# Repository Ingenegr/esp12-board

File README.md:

# esp12-board
esp-12 Board Design Eagle File

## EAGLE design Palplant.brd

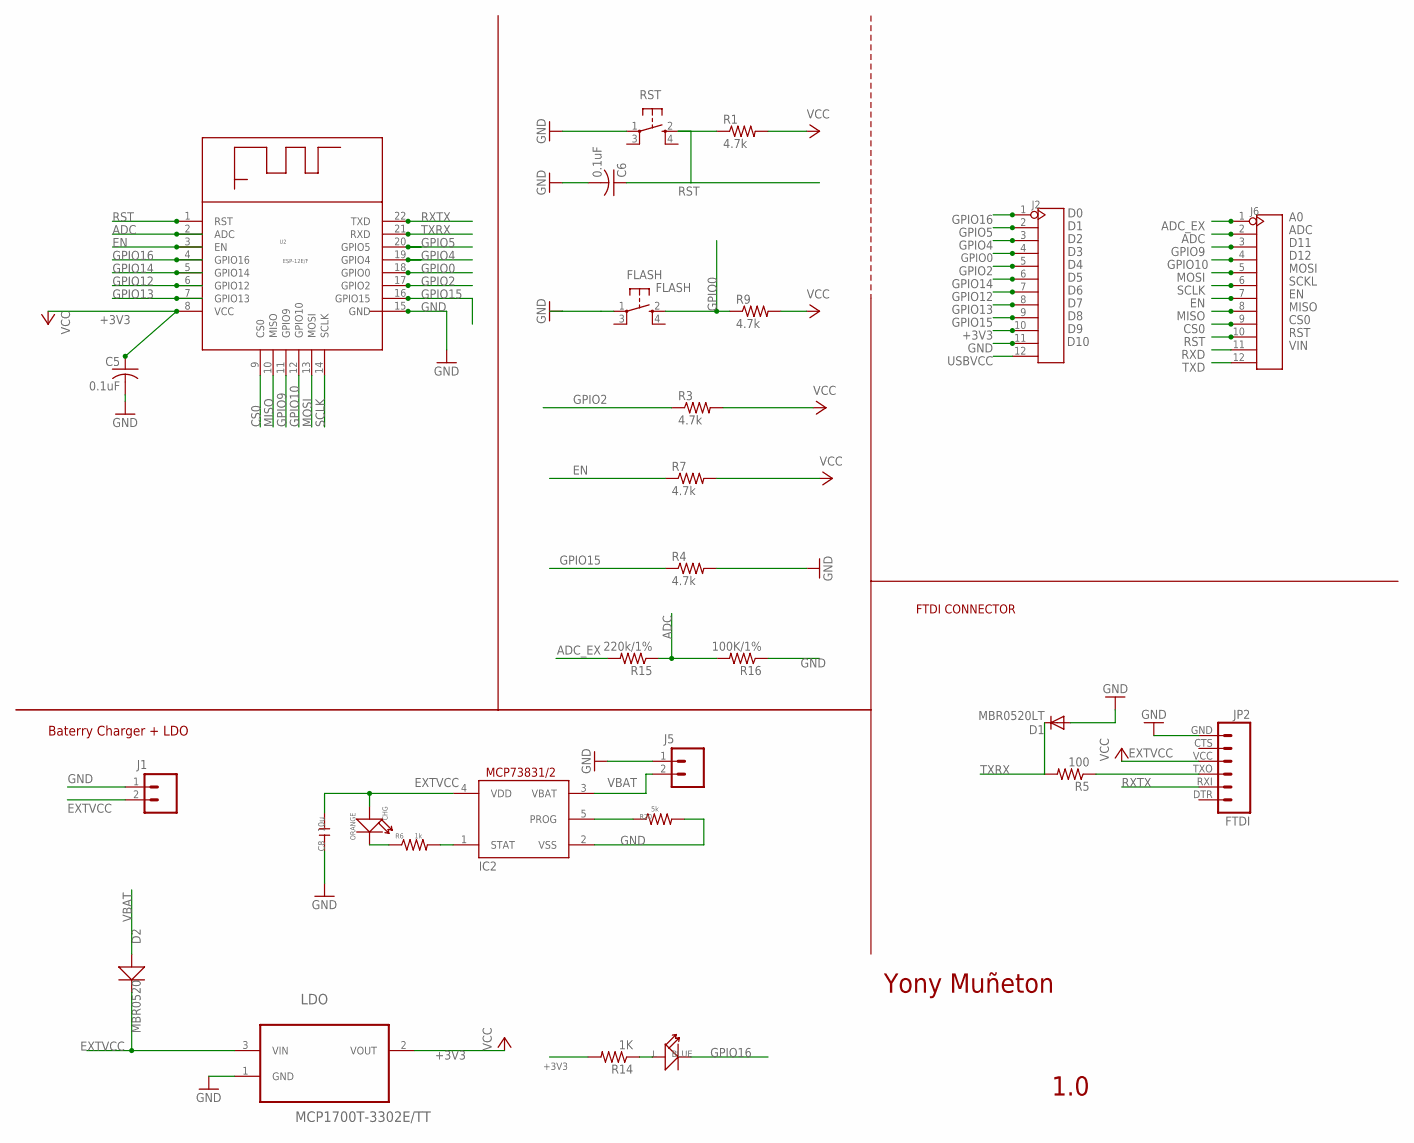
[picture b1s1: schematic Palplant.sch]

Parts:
C5, C6: 0.1uF; C0603; MPN 0805B104M500CT
C8: 10u; C0603
CHG: ORANGE; D0603
D1: MBR0520LT; SOD123; MPN 1N4004RLG
D2: MBR0520; SOD123
FLASH: FLASH; KMR2; MPN KMR221G LFS
IC2: MCP73831/OT; SOT23-5L
J1, J5: M02-JST-2MM-SMT; JST-2-SMD
J2, J6: HEADER-12P-2.54; 12P-2.54
JP2: FTDI; FTDI_BASIC; MPN 2214S-06SG-85
L: BLUE; LED-0603
LDO: MCP1700T-3302E/TT; SOT95P237X112-3N
R1, R3, R4, R7, R9: 4.7k; R0603; MPN MC0805S8F4701T5E
R5: 100; R0603; MPN ERJ-6ENF1002V
R6: 1k; R0603
R14: 1K; R0603
R15: 220k/1%; R0603
R16: 100K/1%; R0603
R20: 5k; R0603
RST: SPST_TACT-KMR2; KMR2; MPN KMR221G LFS
U2: ESP-12E/F

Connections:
+3V3: C5.1, J2.10, LDO.2 (VOUT), R1.2, R3.2, R7.2, R9.2, R14.2, U2.8 (VCC)
ADC: J6.2, R15.1, R16.2, U2.2 (ADC)
ADC_EX: J6.1, R15.2
CS0: J6.9, U2.9 (CS0)
EN: J6.7, R7.1, U2.3 (EN)
EXTVCC: C8.2, CHG.+, D2.-, IC2.4 (VDD), J1.2, JP2.VCC (4), LDO.3 (VIN)
GND: C5.2, C6.2, C8.1, D1.A, FLASH.1, IC2.2 (VSS), J1.1, J2.11, J5.1, JP2.GND (6), LDO.1 (GND), R4.2, R16.1, R20.2, RST.1, U2.15 (GND)
GPIO0: FLASH.2 (S), J2.4, R9.1, U2.18 (GPIO0)
GPIO2: J2.5, R3.1, U2.17 (GPIO2)
GPIO4: J2.3, U2.19 (GPIO4)
GPIO5: J2.2, U2.20 (GPIO5)
GPIO9: J6.3, U2.11 (GPIO9)
GPIO10: J6.4, U2.12 (GPIO10)
GPIO12: J2.7, U2.6 (GPIO12)
GPIO13: J2.8, U2.7 (GPIO13)
GPIO14: J2.6, U2.5 (GPIO14)
GPIO15: J2.9, R4.1, U2.16 (GPIO15)
GPIO16: J2.1, L.-, U2.4 (GPIO16)
MISO: J6.8, U2.10 (MISO)
MOSI: J6.5, U2.13 (MOSI)
unnamed: L.+, R14.1
unnamed: CHG.-, R6.1
unnamed: JP2.TXO (3), R5.1
unnamed: IC2.1 (STAT), R6.2
unnamed: IC2.5 (PROG), R20.1
RST: C6.1, J6.10, R1.1, RST.2 (S), U2.1 (RST)
RXD: J6.11
RXTX: JP2.RXI (2), U2.22 (TXD)
SCLK: J6.6, U2.14 (SCLK)
TXD: J6.12
TXRX: D1.C, R5.2, U2.21 (RXD)
USBVCC: J2.12
VBAT: D2.+, IC2.3 (VBAT), J5.2

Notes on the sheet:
Yony Muñeton
1.0
FTDI CONNECTOR
Baterry Charger + LDO
D10
D11
ADC
CS0
MISO
MOSI
SCKL
D12
RST
VIN

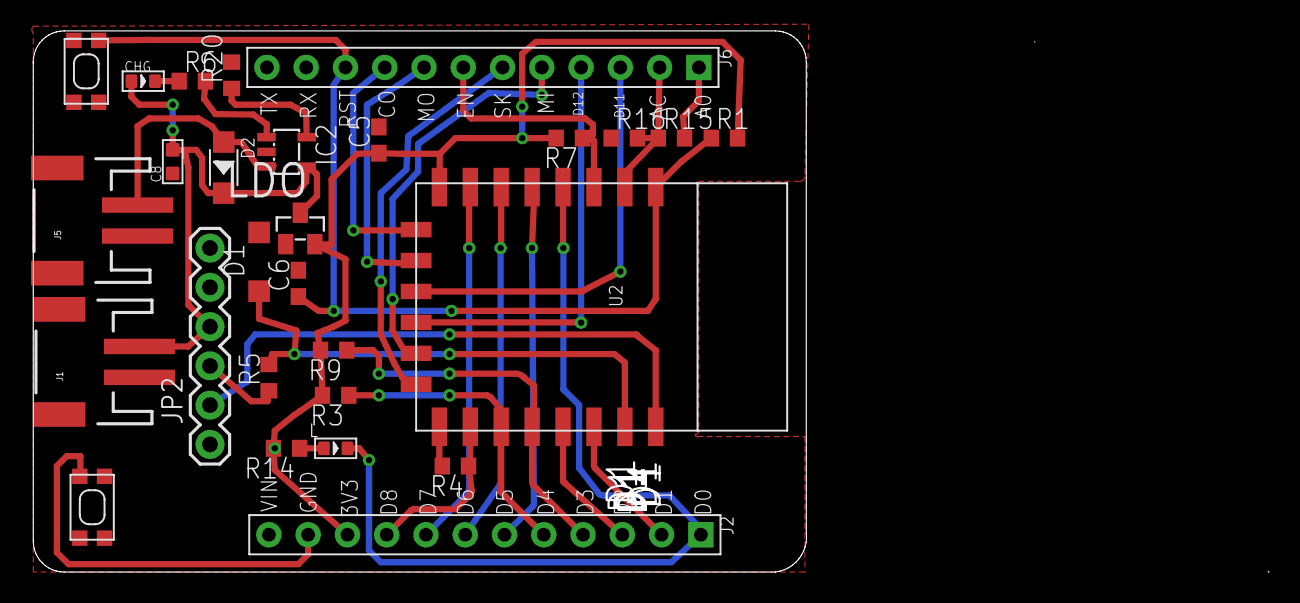
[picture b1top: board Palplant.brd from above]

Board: 2 copper layers, 79.9 x 35.0 mm, 28 parts (0 on the bottom side), 30 nets.

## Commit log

2016-11-21 First Commmit Initial Files board and schema
2016-11-22 The resistor now use the same reference and package

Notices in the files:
parts and their libraries:
SparkFun: Licensing: CC v3.0 Share-Alike You are welcome to use this library for commercial purposes.
